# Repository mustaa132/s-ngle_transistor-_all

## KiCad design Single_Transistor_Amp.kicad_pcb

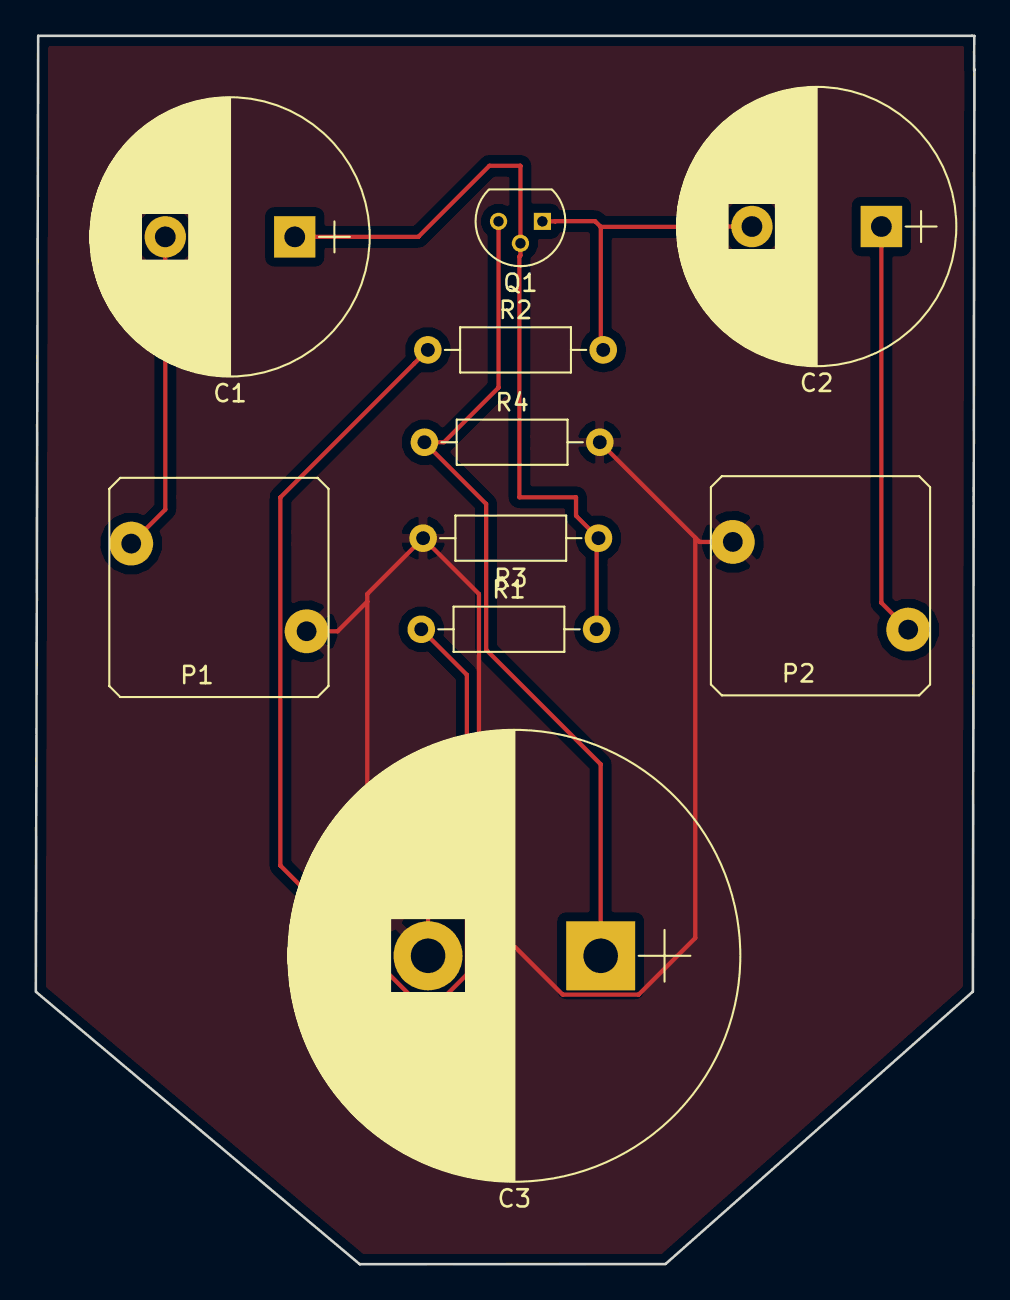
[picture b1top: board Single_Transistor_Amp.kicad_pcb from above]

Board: 2 copper layers, 54.4 x 71.2 mm, 10 parts (0 on the bottom side), 7 nets.

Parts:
C1, C2: 20uF; CP_Radial_D16.0mm_P7.50mm
C3: 50uF; CP_Radial_D26.0mm_P10.00mm_SnapIn
P1, P2: CONN_01X02; SW_PUSH
Q1: BC547; TO-92_Molded_Narrow
R1: 22k; R_Axial_DIN0207_L6.3mm_D2.5mm_P10.16mm_Horizontal
R2, R3, R4: R; R_Axial_DIN0207_L6.3mm_D2.5mm_P10.16mm_Horizontal

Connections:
+12V: R1.1, R2.1
GND: C3.2, P1.1, P2.2, R3.2, R4.2
unnamed: C1.1, Q1.2, R1.2, R3.1
unnamed: C1.2, P1.2
unnamed: C2.1, P2.1
unnamed: C2.2, Q1.1, R2.2
unnamed: C3.1, Q1.3, R4.1

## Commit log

2017-05-24 Mustafa_Yıldız_Sıngle_transıstor_amp_all
2017-05-24 Mustafa_yildiz_single_transistor_amp_all
